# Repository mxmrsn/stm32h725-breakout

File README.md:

# STM32H725-Breakout

## Flash Layout
The memory of the chip is configured where the first 128kB are dedicated to the bootloader, then the rest is for the main application. Seee in ```../bootloader/Core/Src/main.c```:

```
#define APP_ADDRESS 0x08020000
```

## Clock Configuration
The clock is optimized to run 48MHz on the USB comms, and ~530Hz main clock rate.

## DFU Trigger
To put the chip into bootloader mode, we configure this by holding GPIO PC10 button down. Then the LED connected to GPIO PC11 should heartbeat at 1Hz.

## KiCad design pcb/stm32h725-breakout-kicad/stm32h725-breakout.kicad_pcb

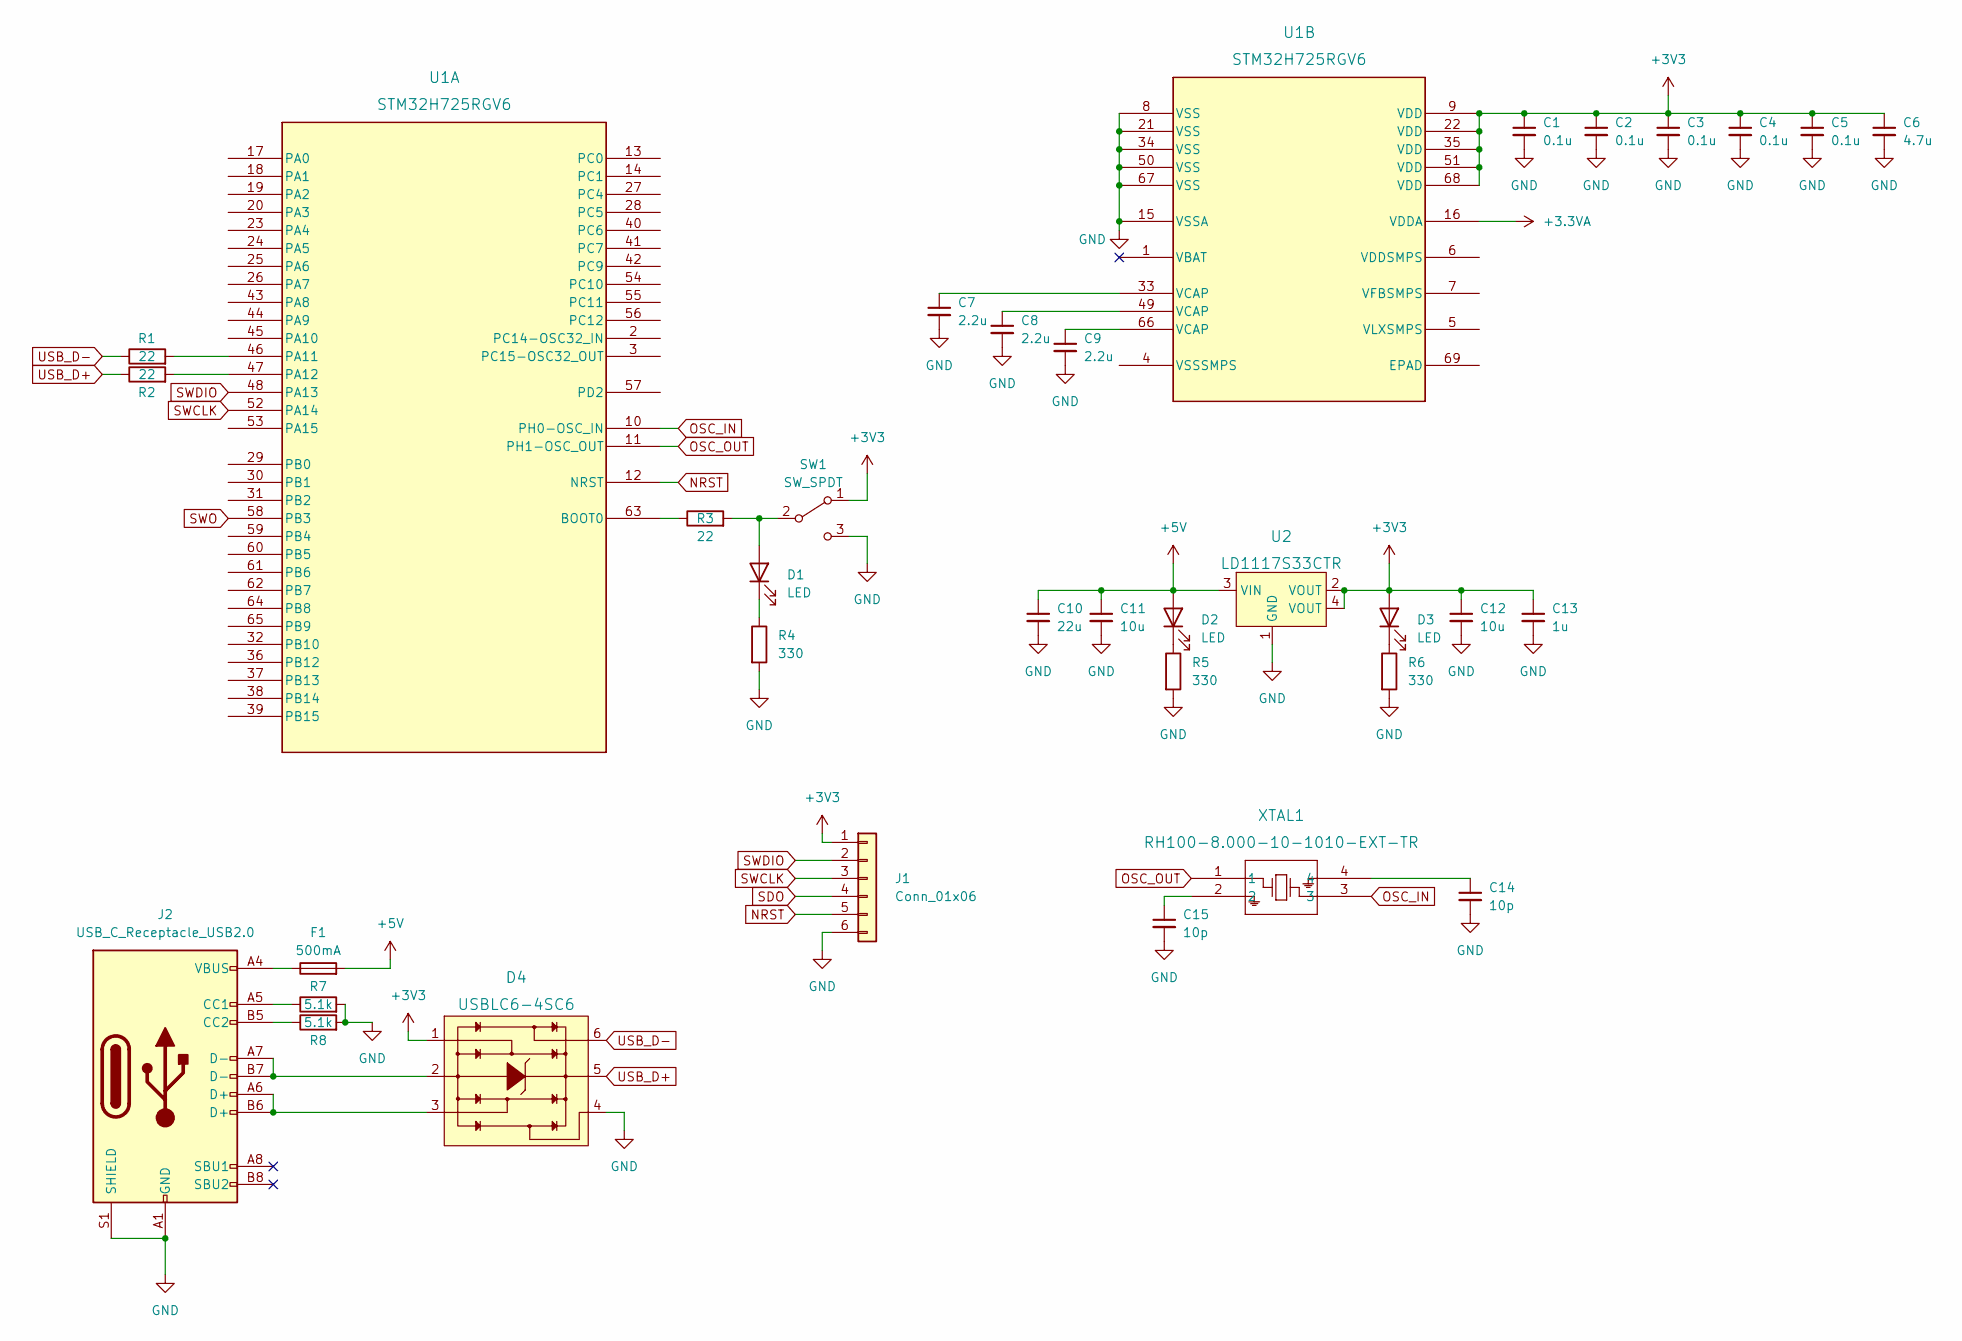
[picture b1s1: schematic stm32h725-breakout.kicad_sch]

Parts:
C1, C2, C3, C4, C5: 0.1u; C_0603_1608Metric
C6: 4.7u; C_0603_1608Metric
C7, C8, C9: 2.2u; C_0603_1608Metric
C10: 22u; C_0603_1608Metric
C11, C12: 10u; C_0603_1608Metric
C13: 1u; C_0603_1608Metric
C14, C15: 10p; C_0603_1608Metric
D1: LED
D2, D3: LED; LED_0805_2012Metric
D4: USBLC6-4SC6; SOT23-6L; MPN USBLC6-4SC6; Digi-Key_PN 497-4492-1-ND
F1: 500mA; Fuse_0805_2012Metric
J1: Conn_01x06; Hirose_FH12-8S-0.5SH_1x08-1MP_P0.50mm_Horizontal
J2: USB_C_Receptacle_USB2.0
R1, R2, R3: 22; R_0603_1608Metric
R4, R5, R6: 330; R_0603_1608Metric
R7, R8: 5.1k; R_0603_1608Metric
SW1: SW_SPDT; SW_SPST_B3U-1000P
U1: STM32H725RGV6; VFQFPN68_8x8mm_STM
U2: LD1117S33CTR; SOT-223; MPN LD1117S33CTR; Digi-Key_PN 497-1241-1-ND
XTAL1: RH100-8.000-10-1010-EXT-TR; RH100_RAL

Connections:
+3.3VA: U1.16 (VDDA)
+3V3: C1.1, C2.1, C3.1, C4.1, C5.1, C6.1, C12.1, C13.1, D3.2 (A), D4.1, J1.1, SW1.1 (A), U1.9 (VDD), U1.22 (VDD), U1.35 (VDD), U1.51 (VDD), U1.68 (VDD), U2.2 (VOUT), U2.4 (VOUT)
+5V: C10.1, C11.1, D2.2 (A), F1.2, U2.3 (VIN)
GND: C1.2, C2.2, C3.2, C4.2, C5.2, C6.2, C7.2, C8.2, C9.2, C10.2, C11.2, C12.2, C13.2, C14.2, C15.2, D4.4, J1.6, J2.A1 (GND), J2.A12 (GND), J2.B1 (GND), J2.B12 (GND), J2.S1 (SHIELD), R4.2, R5.2, R6.2, R7.2, R8.2, SW1.3 (C), U1.8 (VSS), U1.15 (VSSA), U1.21 (VSS), U1.34 (VSS), U1.50 (VSS), U1.67 (VSS), U2.1 (GND)
NRST: J1.5, U1.12 (NRST)
unnamed: C7.1, U1.33 (VCAP)
unnamed: C8.1, U1.49 (VCAP)
unnamed: C9.1, U1.66 (VCAP)
unnamed: C14.1, XTAL1.4
unnamed: C15.1, XTAL1.2
unnamed: D1.1 (K), R4.1
unnamed: D1.2 (A), R3.2, SW1.2 (B)
unnamed: D2.1 (K), R5.1
unnamed: D3.1 (K), R6.1
unnamed: F1.1, J2.A4 (VBUS), J2.A9 (VBUS), J2.B4 (VBUS), J2.B9 (VBUS)
unnamed: J2.A5 (CC1), R7.1
unnamed: D4.3, J2.A6 (D+), J2.B6 (D+)
unnamed: D4.2, J2.A7 (D-), J2.B7 (D-)
unnamed: J2.B5 (CC2), R8.1
unnamed: R3.1, U1.63 (BOOT0)
unnamed: R1.2, U1.46 (PA11)
unnamed: R2.2, U1.47 (PA12)
OSC_IN: U1.10 (PH0-OSC_IN), XTAL1.3
OSC_OUT: U1.11 (PH1-OSC_OUT), XTAL1.1
SDO: J1.4
SWCLK: J1.3, U1.52 (PA14)
SWDIO: J1.2, U1.48 (PA13)
SWO: U1.58 (PB3)
USB_D+: D4.5, R2.1
USB_D-: D4.6, R1.1

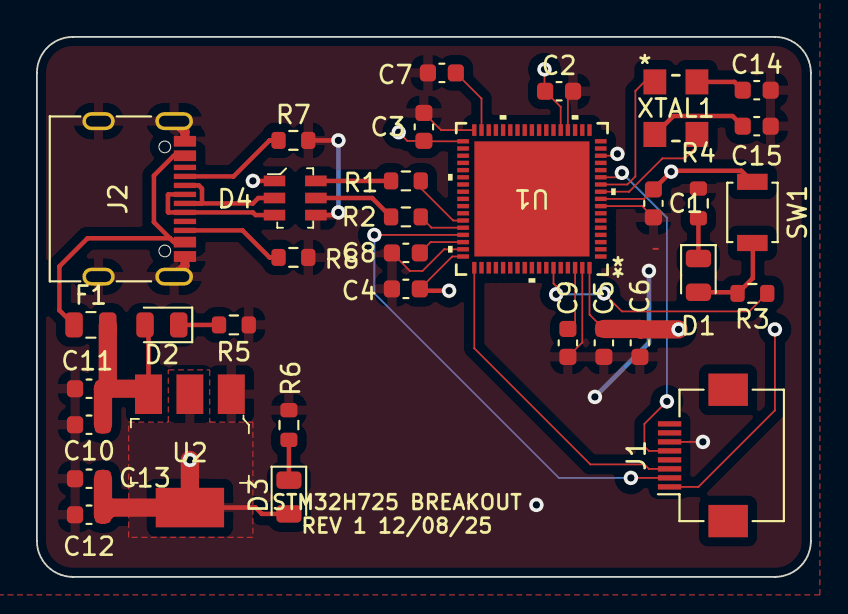
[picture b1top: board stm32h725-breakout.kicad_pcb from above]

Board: 2 copper layers, 43.0 x 30.0 mm, 34 parts (0 on the bottom side), 27 nets.

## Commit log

2025-12-24 added pic to readme
2025-12-24 added chip configuration ioc
2025-12-24 added png
2025-12-24 added pcb files
